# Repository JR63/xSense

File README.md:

# xSense
Telemetrie Sensor basierend auf OpenXSensor

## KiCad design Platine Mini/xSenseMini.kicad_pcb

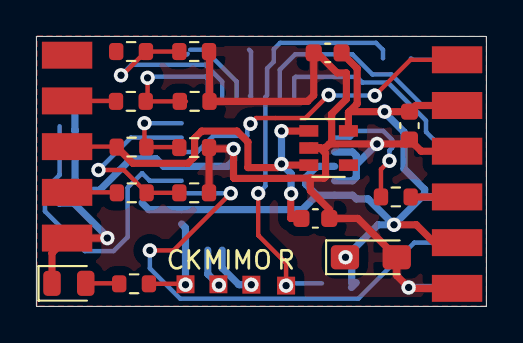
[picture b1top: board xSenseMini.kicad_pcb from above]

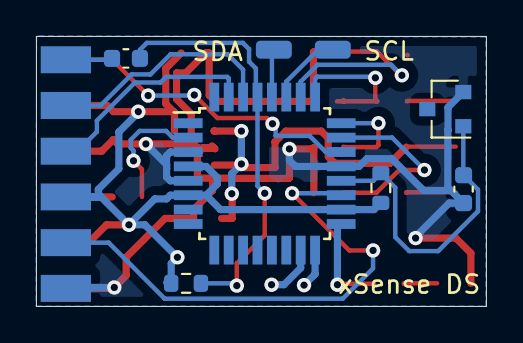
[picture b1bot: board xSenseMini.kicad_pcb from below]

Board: 2 copper layers, 25.0 x 15.0 mm, 31 parts (9 on the bottom side), 25 nets.

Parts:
C1, C2, C4, C5, C6: 100nF; C_0603_1608Metric
C3: 10µF; CP_EIA-3216-10_Kemet-I_Pad1.58x1.35mm_HandSolder
D1: LED; LED_0805_2012Metric
J1: Balancer; SolderPad_5x
J2: Conn_01x06_Male; SolderPad_6x
J3: Serial_AIn; SolderPad_6x
R3: 560; R_0603_1608Metric
R4: 4K7; R_0603_1608Metric
R5, R11: 1K; R_0603_1608Metric
R6: 10k; R_0603_1608Metric
R7, R8, R9, R10: 2,7K; R_0603_1608Metric
R12: 4,7K; R_0603_1608Metric
R13: 10K; R_0603_1608Metric
R14: 12K; R_0603_1608Metric
TP1: Reset; SolderPad_1x1mm
TP2: MOSI; SolderPad_1x1mm
TP3: MISO; SolderPad_1x1mm
TP4: CLK; SolderPad_1x1mm
TP5: SDA; SolderWirePad_1x01_SMD_1x2mm
TP6: SCL; SolderWirePad_1x01_SMD_1x2mm
U1: SPX3819 3,3V; SOT-23-5
U2: LM4040 2.5; SOT-23
U3: ATmega328P-AU; TQFP-32_7x7mm_P0.8mm

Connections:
+3V3: C2.1, C3.1, C5.2, J2.2, J2.5, J3.4, R3.1, R6.2, U1.5, U3.4, U3.6, U3.18
AIn: J3.5, U3.19
CLK: R5.1, TP4.1, U3.17
Curr: J2.1, U3.22
GND: C1.2, C2.2, C3.2, C4.2, C5.1, D1.1, J1.1, J2.3, J2.6, J3.6, R7.2, R8.2, R9.2, R10.2, U1.2, U2.2, U3.3, U3.5, U3.21
MISO: TP3.1, U3.16
MOSI: TP2.1, U3.15
unnamed: C4.1, R3.2, U2.1, U3.20
unnamed: D1.2, R5.2
unnamed: J1.2, R11.1
unnamed: J1.4, R13.1
unnamed: J1.5, R14.1
unnamed: R4.2, U3.2
unnamed: TP5.1, U3.27
unnamed: TP6.1, U3.28
Reset: C6.2, R6.1, TP1.1, U3.29
ResetSer: C6.1, J3.1
Rx: J3.2, U3.30
Tele: J2.4, R4.1
Tx: J3.3, U3.31
Z1: R7.1, R11.2, U3.23
Z2: R8.1, R12.2, U3.24
Z2Vcc: C1.1, J1.3, R12.1, U1.1, U1.3
Z3: R9.1, R13.2, U3.25
Z4: R10.1, R14.2, U3.26

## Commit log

2021-01-10 Initialer Commit
2021-01-11 + Datenblätter + Initaler Upload xSense Mini
2021-01-11 + Solder Pads hinzugefügt
2021-01-11 + Update xSense Mini + Fixes SolderPads + 1x1 Mini Lötpad
2021-01-11 + Schaltplan Mini Update + Komplett neu geroutet und finalisiert
